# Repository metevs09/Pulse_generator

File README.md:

# Pulse_generator

This study is the circuit diagram and board layout obtained by reverse engineering a pulse generator integrated circuit.

In future designs, a new circuit will be added in a new repo with improvements such as circuit voltage regulator and photocoupler.

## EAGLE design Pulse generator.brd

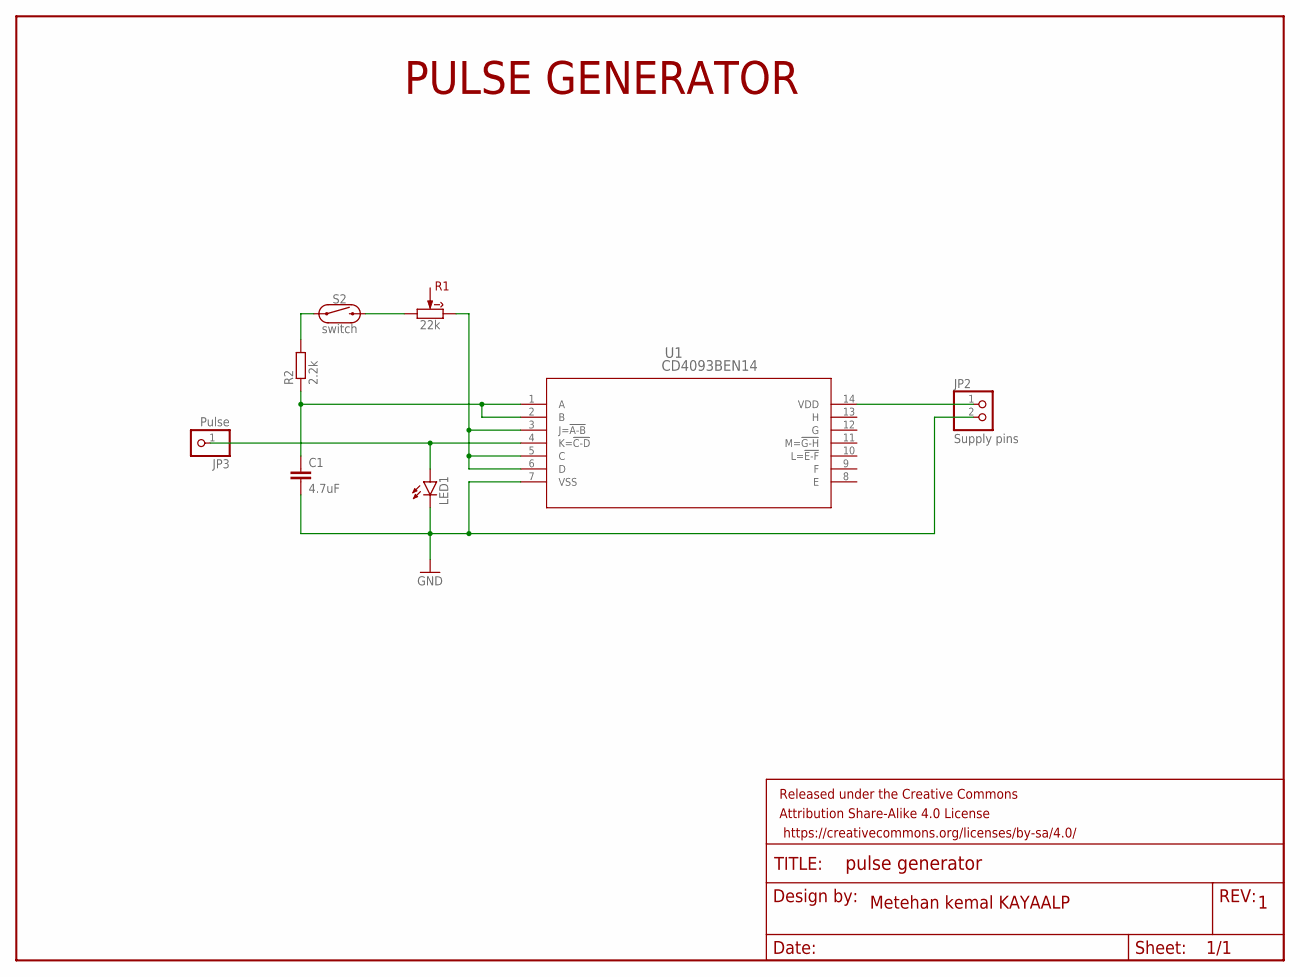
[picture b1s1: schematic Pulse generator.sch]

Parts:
C1: 4.7uF; C2.5-3
FRAME1: FRAME-LETTER; CREATIVE_COMMONS
JP2: Supply pins; 1X02
JP3: Pulse; 1X01
LED1: LED5MM
R1: 22k; PTD901
R2: 2.2k; 0204V
S2: switch; REED_SWITCH_PLASTIC
U1: CD4093BEN14; N14

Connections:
GND: C1.2, JP2.2, LED1.K (C), U1.7 (VSS)
unnamed: JP2.1, U1.14 (VDD)
unnamed: C1.1, R2.1, U1.1 (A), U1.2 (B)
unnamed: R1.3 (CW), U1.3 (J=!A-B), U1.5 (C), U1.6 (D)
unnamed: R2.2, S2.P$1 (1)
unnamed: R1.1 (CCW), S2.P$2 (2)
unnamed: JP3.1, LED1.A, U1.4 (K=!C-D)

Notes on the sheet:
PULSE GENERATOR
Metehan kemal KAYAALP

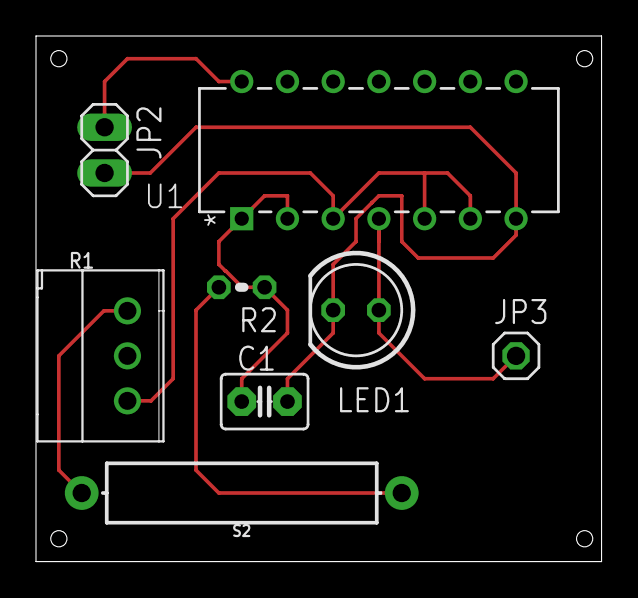
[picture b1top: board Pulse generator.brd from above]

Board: 2 copper layers, 31.4 x 29.2 mm, 9 parts (0 on the bottom side), 7 nets.

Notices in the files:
parts and their libraries:
SparkFun-Aesthetics: Licensing: Creative Commons ShareAlike 4.0 International - https://creativecommons.org/licenses/by-sa/4.0
SparkFun-Aesthetics: Released under the Creative Commons Attribution Share-Alike 4.0 License
SparkFun-Aesthetics: https://creativecommons.org/licenses/by-sa/4.0
